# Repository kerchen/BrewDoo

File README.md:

# BrewDoo
A timer for keeping track of how old a pot of coffee is

For a full project write-up, please visit http://whirlingchair.com/brewdoo-a-coffee-age-timer.html

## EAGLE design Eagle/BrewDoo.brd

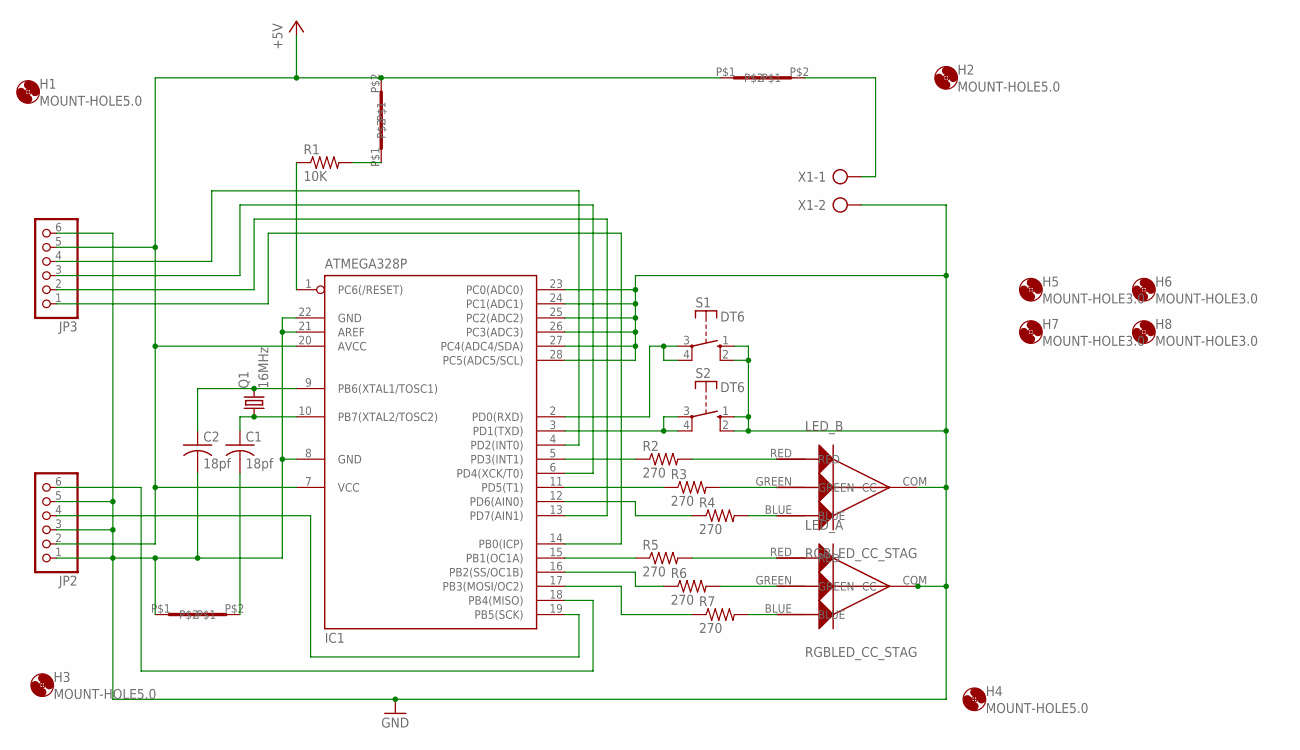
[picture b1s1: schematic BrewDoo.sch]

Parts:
C1, C2: 18pf; C025-025X050
H1, H2, H3, H4: MOUNT-HOLE5.0; 5,0
H5, H6, H7, H8: MOUNT-HOLE3.0; 3,0
IC1: ATMEGA328P; DIL28-3
JP2, JP3: PINHD-1X6; 1X06
LED_A: RGBLED_CC_STAG; RGBLED_STAGG
LED_B: RGBLED_CC_STAG; RGBLED_STAGG
Q1: 16MHz; HC49/S
R1: 10K; 0204/7
R2: 270; 0207/12
R3, R4: 270; 0207/10
R5, R6, R7: 270; 0207/15
S1, S2: DT6
U$1, U$2: WIRE-0.3
U$3: WIRE-0.6
X1: AK300/2

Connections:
+5V: IC1.7 (VCC), IC1.20 (AVCC), JP2.2, JP3.5, R1.2, U$1.P$1, U$1.P$2, U$3.P$1, U$3.P$2, X1.1
GND: C1.2, C2.2, IC1.8 (GND), IC1.21 (AREF), IC1.22 (GND), IC1.23 (PC0(ADC0)), IC1.24 (PC1(ADC1)), IC1.25 (PC2(ADC2)), IC1.26 (PC3(ADC3)), IC1.27 (PC4(ADC4/SDA)), IC1.28 (PC5(ADC5/SCL)), JP2.1, JP2.3, JP2.5, JP3.6, LED_A.COM (CC), LED_B.COM (CC), S1.1 (S), S1.2 (S), S2.1 (S), S2.2 (S), U$2.P$1, U$2.P$2, X1.2
unnamed: C2.1, IC1.9 (PB6(XTAL1/TOSC1)), Q1.2
unnamed: C1.1, IC1.10 (PB7(XTAL2/TOSC2)), Q1.1
unnamed: IC1.5 (PD3(INT1)), R2.1
unnamed: IC1.2 (PD0(RXD)), S1.3, S1.4
unnamed: LED_B.RED, R2.2
unnamed: IC1.19 (PB5(SCK)), JP2.4
unnamed: IC1.18 (PB4(MISO)), JP2.6
unnamed: IC1.14 (PB0(ICP)), JP3.1
unnamed: IC1.13 (PD7(AIN1)), JP3.2
unnamed: IC1.6 (PD4(XCK/T0)), JP3.3
unnamed: IC1.4 (PD2(INT0)), JP3.4
unnamed: IC1.15 (PB1(OC1A)), R5.1
unnamed: LED_A.GREEN, R6.2
unnamed: IC1.17 (PB3(MOSI/OC2)), R7.1
unnamed: LED_B.GREEN, R3.2
unnamed: LED_B.BLUE, R4.2
unnamed: IC1.11 (PD5(T1)), R3.1
unnamed: IC1.3 (PD1(TXD)), S2.3, S2.4
unnamed: IC1.12 (PD6(AIN0)), R4.1
unnamed: LED_A.RED, R5.2
unnamed: IC1.16 (PB2(SS/OC1B)), R6.1
unnamed: LED_A.BLUE, R7.2
RESET: IC1.1 (PC6(/RESET)), R1.1

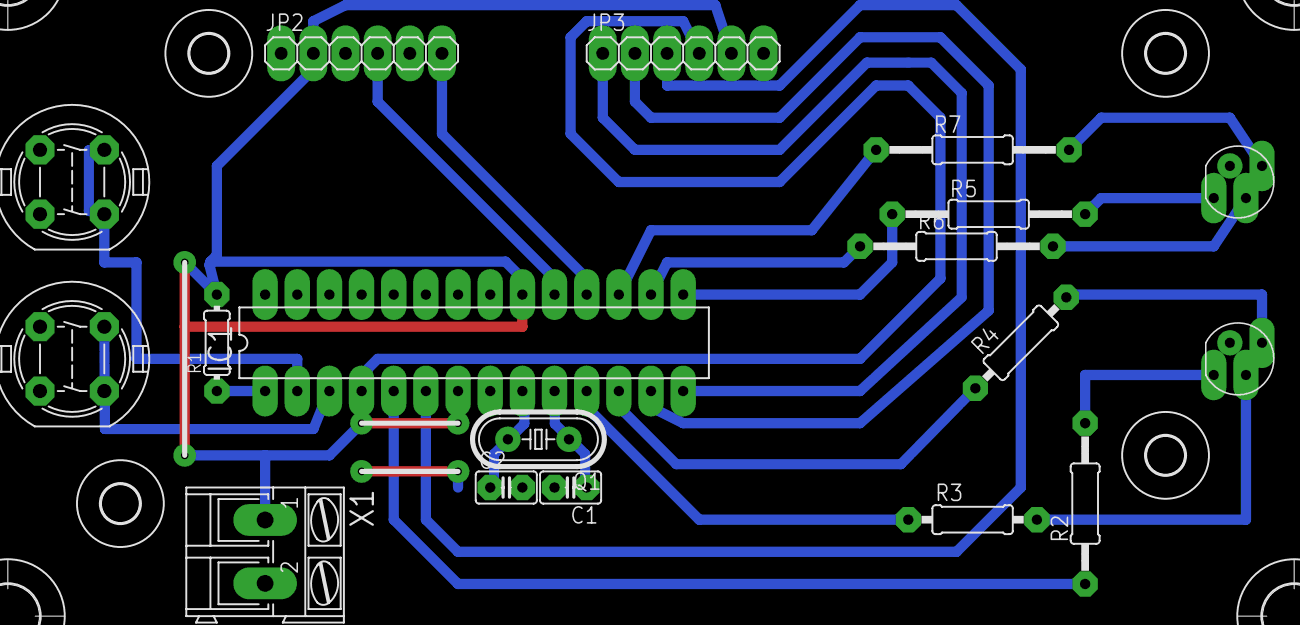
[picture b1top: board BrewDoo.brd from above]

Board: 2 copper layers, 29 parts (0 on the bottom side), 25 nets.

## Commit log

2015-04-08 Initial copy of CubeSign project files
2015-04-09 Implemented display.
2015-04-10 Implemented indicator LEDs; added seconds display; tested with hardware
2015-04-10 Set brew time limit to something more realistic
2015-04-10 More tweaks and minor improvements
2015-04-10 Fixed bug preventing proper LED coloring from working; removed 'old' display in favor of limiting how long time is shown before it is reset
2015-04-12 First cut at PCB layout
2015-04-12 Version 1.0.
2015-04-16 Added enclosure gcode
2015-04-22 Documentation stuff
2015-04-23 Fixed writeup URL
2015-05-10 Version 1.1: Introduced solid green time before interpolation begins
